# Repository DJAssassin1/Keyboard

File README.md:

# Macro Keyboard
Just typical macro keyboard. It uses Deej for changing the volume of a current open window.

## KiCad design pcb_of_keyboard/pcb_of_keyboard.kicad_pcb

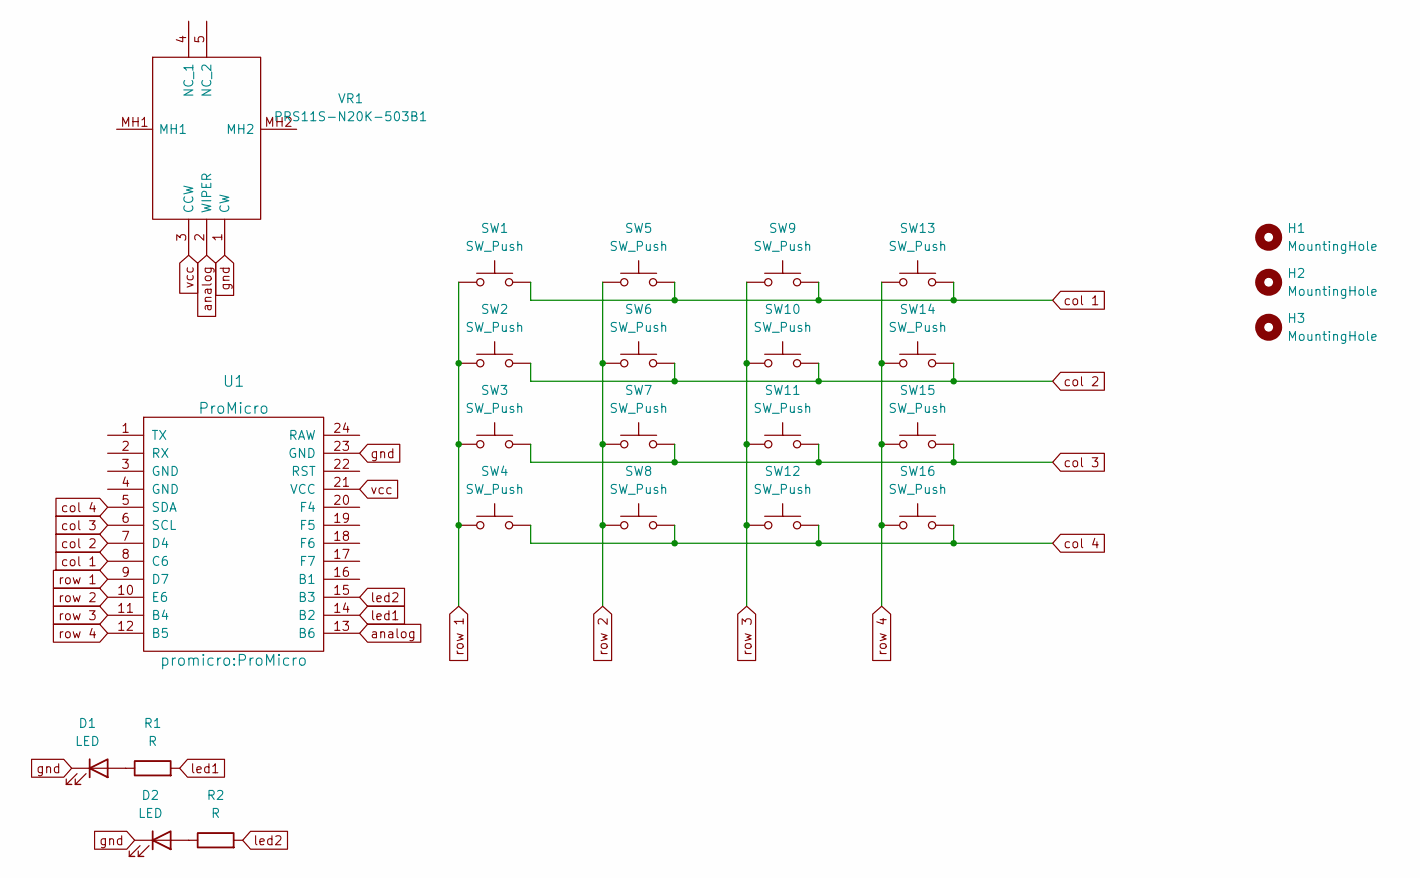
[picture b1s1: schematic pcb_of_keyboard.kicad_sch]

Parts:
D1, D2: LED; LED_0805_2012Metric_Pad1.15x1.40mm_HandSolder
H1, H2, H3: MountingHole; MountingHole_2.7mm
R1, R2: R; R_0805_2012Metric_Pad1.20x1.40mm_HandSolder
SW1, SW2, SW3, SW4, SW5, SW6, SW7, SW8, SW9, SW10, SW11, SW12, SW13, SW14, SW15, SW16: SW_Push; SW_Cherry_MX_1.00u_PCB
U1: ProMicro
VR1: PRS11S-N20K-503B1; PRS11SN20K503B1; Manufacturer_Part_Number PRS11S-N20K-503B1; Mouser Part Number 652-PRS11SN20K503B1

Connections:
unnamed: D1.2 (A), R1.1
unnamed: D2.2 (A), R2.1
analog: U1.13 (B6), VR1.2 (WIPER)
col 1: SW1.2, SW5.2, SW9.2, SW13.2, U1.8 (C6)
col 2: SW2.2, SW6.2, SW10.2, SW14.2, U1.7 (D4)
col 3: SW3.2, SW7.2, SW11.2, SW15.2, U1.6 (SCL)
col 4: SW4.2, SW8.2, SW12.2, SW16.2, U1.5 (SDA)
gnd: D1.1 (K), D2.1 (K), U1.23 (GND), VR1.1 (CW)
led1: R1.2, U1.14 (B2)
led2: R2.2, U1.15 (B3)
row 1: SW1.1, SW2.1, SW3.1, SW4.1, U1.9 (D7)
row 2: SW5.1, SW6.1, SW7.1, SW8.1, U1.10 (E6)
row 3: SW9.1, SW10.1, SW11.1, SW12.1, U1.11 (B4)
row 4: SW13.1, SW14.1, SW15.1, SW16.1, U1.12 (B5)
vcc: U1.21 (VCC), VR1.3 (CCW)

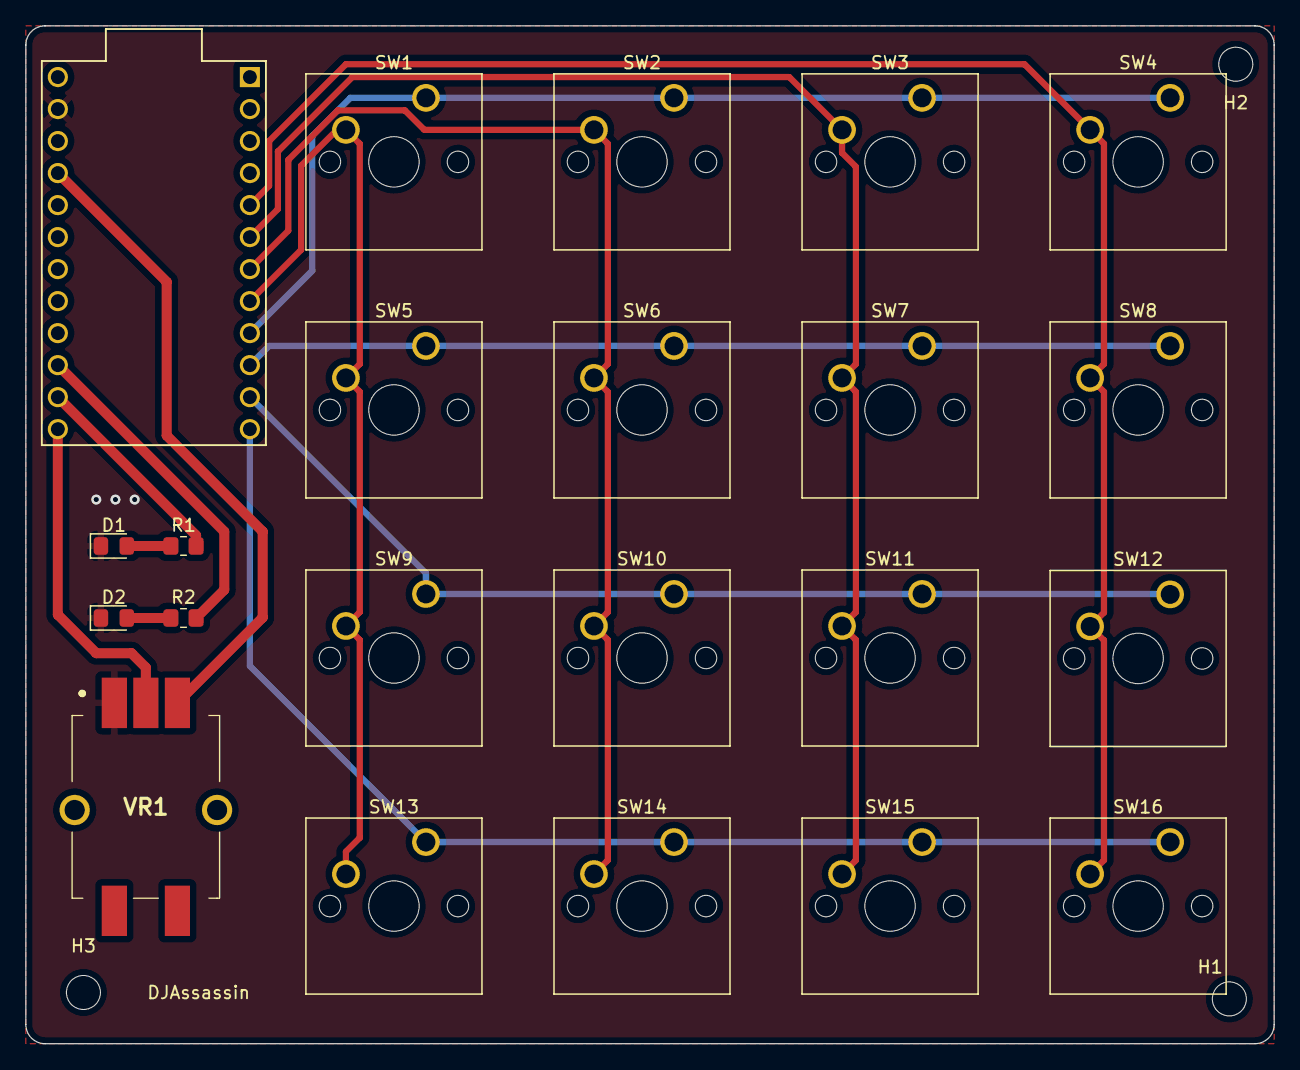
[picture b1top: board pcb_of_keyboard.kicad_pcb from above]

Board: 2 copper layers, 99.1 x 80.8 mm, 25 parts (1 on the bottom side), 15 nets.

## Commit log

2022-04-04 prvni commit
2023-10-14 predelani
2023-10-14 uprava 2
2023-10-14 pridani pcb schema
